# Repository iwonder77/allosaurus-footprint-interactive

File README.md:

# Allosaurus Footprint Stomp Pad Interactive

Three-channel, optically-isolated 24 V input board plus ESP32 show controller that turns industrial safety mats ("stomp pads") into clean, debounced triggers for synchronized video and LED strip output at the Need for Speed exhibit in Thanksgiving Point's Museum of Ancient Life. A visitor stomps a footprint mat, and the matching dinosaur's clip plays with an accompanying light strip animation around that Allosaurus' femur bone cast.

---

## At a Glance

|                       |                                                                                                 |
| --------------------- | ----------------------------------------------------------------------------------------------- |
| **Input domain**      | 24 V DC current loop, one per mat (field wiring, up to ~10 ft)                                  |
| **Logic domain**      | 3.3 V, shared with the controller (no level shifting needed)                                    |
| **Channels / mats**   | 3 - `hatchling`, `juvenile`, `adult` (one per footprint mat)                                    |
| **Input per channel** | ASOSafety safety mat (normally-open, passive dry contact)                                       |
| **Isolation**         | onsemi **H11L1M** optocoupler - one per channel                                                 |
| **Controller**        | **ESP32-DevKitC** (`fqbn: esp32:esp32:esp32`) firmware sketch in `esp32/`                       |
| **Input logic**       | Mat pressed → `Vo` LOW (**active-low**, external pull-up idles HIGH)                            |
| **Output banks**      | Media (BrightSign) + LED Light Strip (controlled by QuinLED), both **active-low** 200 ms pulses |
| **Show rule**         | First stomp wins; all mats locked out until that clip finishes                                  |
| **PCB**               | `2-layer, JLCPCB fab + assembly`                                                                |
| **Status**            | PCB version June 2026 designed (see `ERRATA.md`) · firmware complete                            |

---

---

## Overview

The Allosaurus Footprint interactive lets visitors stomp on floor-mounted pads to trigger a short video, audio, and light response - a video clip on a BrightSign player and an LED-strip animation on a QuinLED driver - fired in sync from a single step. Each pad is an **industrial normally-open safety mat used here purely as a rugged foot switch** in order to run unattended 24/7 in an abusive museum exhibit environment.

The obvious approach is to wire each mat's dry contact straight into a GPIO with the internal pull-up and debounce in firmware. That may work on a bench, but is not the bullet proof solution on the floor for the following reasons:

- The mats sit **up to ~10 ft** from the controller.
- The exhibit must run **24/7, unattended, for years**, with **hundreds of activations a day** and cannot experience any brown-out or mat trigger failures.
- Hundreds of visitors means hundreds of potential **ESD events** onto the mat wiring.
- Industrial-rated mats need a "wetting" current to ensure reliable long-term operation of the dry contacts (part of the reason manufacturers specify connecting to a 24V system)

A bare high-impedance GPIO sense on a 10 ft run is an antenna prone to noise pickup and false triggers. The optoisolation board I designed was a cheap bulletproof add-on to solves both problems at the input stage, so the controller only ever sees a clean, isolated, logic-level edge - then the firmware does debounce, fault detection, and show sequencing on top.

---

# Hardware

## Hardware Design Requirements

The input board needed to:

- Convert a passive N.O. mat closure into a reliable 3.3 V logic trigger.
- Provide **galvanic isolation** between the 24 V field wiring and the 3.3 V logic, so ground offsets and transients on the mat side cannot reach the MCU.
- Resist false triggers from noise coupled onto the long mat cabling.
- Give maintenance staff a **visible per-channel indicator** to confirm at a glance that a mat is being pressed and its sense path is driven.
- Be manufacturable at JLCPCB (fab + assembly) with clean, auditable part placement and silkscreen labels.
- Run for years with essentially zero maintenance.

These led to a **24 V current loop driving an optocoupler per channel**: the current loop resists noise, adds a bit of "wetting" current, and the optocoupler provides isolation plus a clean Schmitt-trigger output edge for the show controller.

## Main Hardware Components

- onsemi **H11L1M** optocoupler - integrated **Schmitt-trigger, open-collector, logic-compatible** output
- **1N4148W** small-signal diode - reverse-polarity protection across the optocoupler input
- Visible indicator LED (green SMD) - per channel, on the input side
- Current-limiting resistors, pull-up resistors, decoupling/filter capacitors (see **Design Notes**)

The full BOM lives in `manufacturing/`.

## Full Schematic

## Main Hardware Architecture

The three channels are identical.

**Input side (referenced to `GND1`, the 24 V ground):**

```
+24V ── mat (N.O.) ── R_series ── [indicator LED] ── H11L1M IR LED ── GND1
                 └── D2 (1N4148W) across the LED string, reverse protection
```

While someone stands on the mat the contact closes and current flows, driving the H11L1M input IR LED and lighting the visible indicator - so the indicator doubles as direct confirmation the sense LED is driven.

> **Note:** rev 1 places the indicator LED _in series_ with the IR LED. This works but is being revised to a parallel branch - see **Hardware Revisions** and `ERRATA.md`.

**Output side (referenced to `GND2`, the 3.3 V ground):**

```
+3V3 ── R_pullup (2.2 kΩ) ──┬── Vo (H11L1M open-collector) ── ESP32 GPIO
                            └── C1 (0.1 µF) noise filter to GND2
+3V3 ── C2 (0.1 µF) decoupling, close to the H11L1M VCC pin ── GND2
```

The output is **active-low on a press**: pressed → IR LED on → output transistor on → `Vo` LOW. Idle → `Vo` pulled HIGH by the 2.2 kΩ. The output-side `VCC` shares the 3.3 V rail with the MCU so HIGH can never exceed the MCU input rail.

| Mat state        | IR LED | `Vo` node      | GPIO reads | Indicator LED |
| ---------------- | ------ | -------------- | ---------- | ------------- |
| Idle (open)      | off    | HIGH (~3.07 V) | HIGH       | off           |
| Pressed (closed) | on     | LOW (≤ 0.4 V)  | LOW        | lit           |

## Design Notes

### Why a 24 V current loop instead of a bare GPIO

**Current loop, not voltage sense.** Pushing real current (target ~9–10 mA) through the H11L1M input LED is a low-impedance path; noise must overcome actual current to look like a valid change. Far harder to corrupt than a voltage on a high-impedance node over 10 ft.

**Wetting current (bonus).** Meaningful current through the dry mat contacts keeps a **wetting current** flowing, which helps those contacts resist any oxide film that makes aging switches flaky. This sets a _floor_ on the sense-branch current independent of the opto's switching threshold.

### Optocoupler output logic and levels

The H11L1M's integrated Schmitt trigger gives clean, bounce-free edges. Verified against the controller's input thresholds (ESP32 input thresholds are ratios of VDD):

| Parameter                           | Value   | Source                               |
| ----------------------------------- | ------- | ------------------------------------ |
| `V_IH(min)` ≈ 0.75·VDD              | ~2.48 V | ESP32 datasheet                      |
| `V_IL(max)` ≈ 0.25·VDD              | ~0.83 V | ESP32 datasheet                      |
| H11L1M `V_OL`                       | ≤ 0.4 V | datasheet (sinks 16 mA at 0.4 V max) |
| H11L1M output-off leakage `I_OH`    | 100 µA  | datasheet                            |
| H11L1M `V_CC` range (min **3.0 V**) | 3–16 V  | datasheet                            |

With a **2.2 kΩ pull-up**: HIGH ≈ 3.3 − (~105 µA)(2.2 kΩ) ≈ **3.07 V** (~0.6 V over `V_IH`); LOW ≤ **0.4 V** (~0.4 V under `V_IL`); pressed-state sink ≈ 1.3 mA (far below 16 mA). The binding constraint is the HIGH side — the 100 µA leakage droops it — so the pull-up is kept small-ish. `C1` = 0.1 µF with the 2.2 kΩ gives RC ≈ **220 µs**: a **glitch filter, not a debouncer**. Mat bounce runs for milliseconds, so firmware debounce is still mandatory (and the firmware does far more than that - see below).

### Reverse-polarity protection

The 1N4148W spans the forward LED string, reverse-biased in normal use, conducting only on a reversed-polarity miswire. Confirm its orientation (cathode toward +24 V in normal operation). A single series Schottky on the 24 V input is the tidier belt-and-suspenders option if full reverse immunity is ever wanted.

## Hardware Revisions

Two changes are planned for the next board spin. **version June 2026 is functional as-is** - these are improvements, not blockers. Full detail, rationale, and selection guidance live in **[`ERRATA.md`](./ERRATA.md)** next to the rev-1 schematic/PCB files.

- **ERRATA-1: Indicator LED should be parallel, not series.** Version June 2026 shares one loop current between the IR LED and the indicator. Moving the indicator to its own parallel branch (each LED with its own resistor) lets each current be sized independently and stops an open-failed indicator from killing the sense path. **Recompute the opto current when you do**.
- **ERRATA-2: Add a TVS at each mat connector.** Given public foot traffic (ESD) over ~10 ft of exposed cable, 24/7 for years, a unidirectional TVS at each input protects the front-end. (It does _not_ protect the ESP32 - the opto already does that.) Recommended, not required.

## PCB & Manufacturing

**Isolation strategy (the whole point).** `GND1` (24 V) and `GND2` (3.3 V) are separate nets that **never** connect on the board - the only crossing is the opto's light barrier. Two separate bottom-layer copper pours with a ~3 mm gap, the barrier line running through each optocoupler, all three optos oriented identically.

**Mounting holes - verified safe.** The four corner holes carry **no copper** and take plastic standoffs for a custom 3D-printed mount, so hardware can't bridge `GND1` to `GND2`.

**Net classes**

| Class        | Track width | Nets                 |
| ------------ | ----------- | -------------------- |
| `Input_24V`  | 0.5 mm      | `+24V`, `GND1`       |
| `Output_3V3` | 0.3 mm      | `+3V3`, `GND2`, `Vo` |

Both share via 0.6 mm / hole 0.3 mm (0.15 mm annular) and 0.3 mm clearance.

---

# Firmware

`esp32/` — a single non-blocking sketch that reads the three mats, validates each stomp, and fires the matching media + light triggers. No RTOS tasks, no delays; `loop()` runs the whole thing and feeds a hardware watchdog every pass.

## Pinout — `esp32/`

All constants live in `src/Config.h`. Index `i` ties together input `[i]`, media `[i]`, and light `[i]` (mat 1 = hatchling, 2 = juvenile, 3 = adult).

| GPIO     | Direction           | Connects to                         | Constant                |
| -------- | ------------------- | ----------------------------------- | ----------------------- |
| 13       | Input (active-low)  | `Vo1` - hatchling opto output       | `MAT_INPUT_PINS[0]`     |
| 14       | Input (active-low)  | `Vo2` - juvenile opto output        | `MAT_INPUT_PINS[1]`     |
| 15       | Input (active-low)  | `Vo3` - adult opto output           | `MAT_INPUT_PINS[2]`     |
| 21       | Output (active-low) | BrightSign trigger - hatchling clip | `MEDIA_TRIGGER_PINS[0]` |
| 22       | Output (active-low) | BrightSign trigger - juvenile clip  | `MEDIA_TRIGGER_PINS[1]` |
| 23       | Output (active-low) | BrightSign trigger - adult clip     | `MEDIA_TRIGGER_PINS[2]` |
| 16       | Output (active-low) | QuinLED trigger - hatchling strip   | `LIGHT_TRIGGER_PINS[0]` |
| 17       | Output (active-low) | QuinLED trigger - juvenile strip    | `LIGHT_TRIGGER_PINS[1]` |
| 18       | Output (active-low) | QuinLED trigger - adult strip       | `LIGHT_TRIGGER_PINS[2]` |
| 25/26/27 | _reserved_          | former audio bank (WAV Trigger)     | - (do not reuse)        |

## Behavior

**Debounce / validation (per mat).** Three independent timing knobs in `Config.h`, each rejecting a different failure mode — deliberately not collapsed into one value:

| Knob              | Default | Rejects                                                                                 |
| ----------------- | ------- | --------------------------------------------------------------------------------------- |
| `MAT_DEBOUNCE_MS` | 10 ms   | fast edge chatter - line must be stable this long                                       |
| `MAT_MIN_ON_MS`   | 30 ms   | short spikes - press must dwell this long to count (≥ debounce); also the event latency |
| `MAT_REARM_MS`    | 80 ms   | bouncy releases - line must read clear this long to re-arm                              |

**One video at a time (global lockout).** The first validated stomp wins: its clip is triggered and **every** mat input is ignored until that clip finishes, so a video always plays start-to-finish and is never cut off or re-triggered. Lockout = `VIDEO_LENGTH_MS[i]` (13 / 17 / 22 s) + `RETRIGGER_HEADROOM_MS` (1 s) → ~14 / 18 / 23 s. A stomp arriving during a lockout is **discarded**, not queued. This is a different mechanism from `MAT_REARM_MS` (a low-level per-mat cooldown).

**Fail-closed detection.** If a mat reads active continuously for `MAT_STUCK_MS` (10 s - far longer than any real stomp: a welded contact, a stuck mat, or a shorted line), that mat is flagged **faulted**: it stops emitting events and its outputs are forced idle so a stuck input can't leave a device asserted. It auto-recovers after the line reads clear for `MAT_FAULT_RECOVER_MS` (500 ms), re-arming through the boot-safe path.

**Boot-safe.** Each detector starts in `WaitForRelease`, so a mat already held down at power-on never produces a spurious event - it arms only after a confirmed clean release.

**Watchdog.** `loop()` is fully non-blocking and feeds the task watchdog (TWDT) every pass. If anything ever wedges the main task past `WDT_TIMEOUT_MS` (5 s), the watchdog panics and resets the board - the exhibit self-recovers instead of hanging.

## Architecture

The `.ino` handles bring-up (pin setup, watchdog subscribe) and the per-mat loop; the real press logic lives in `src/`.

- **`MatInput`**: a non-blocking, debounced press detector for one active-low opto input, owning only its own state machine (no dependency on Serial or the outputs). `update()` advances it, `eventFired()` latches true exactly once per validated stomp (reading clears it), `pressed()` / `faulted()` / `rawActive()` expose state. The FSM: `WaitForRelease → Armed → PressDebounce → PressConfirm → Held`, with `Faulted` entered from anywhere on a stuck line. Fault and min-on timing are measured against `millis()` marks, so nothing blocks.
- **Main sketch (`esp32.ino`)**: owns one `MatInput` per mat and two output banks (`BANK_MEDIA`, `BANK_LIGHT`) in an index-aligned table, so `triggerMat(i)` fires both of mat `i`'s lines at once and `serviceOutputs()` returns each to idle after the pulse width — non-blocking, so mat scanning never stalls behind an in-flight pulse. It owns the global lockout, logs faults/recoveries once on their edge, and forces a faulted mat's outputs idle. The lockout comparison is rollover-safe (`(int32_t)(now - lockoutUntil) >= 0`).
- **`Config.h`**: single source of truth for pins, polarity, and all timing. `constexpr` throughout (compile-time, zero RAM). Everything you'd tune on the bench lives here so the logic modules stay untouched.

## Deployment & Bring-up

### Flashing

Platform is set in `sketch.yaml` (`esp32:esp32:esp32`). `default_port` is committed as `/dev/cu.usbserial-0001` - **change it to your machine's serial port**, or pass `-p <port>` on upload. A plain `arduino-cli compile` / `upload` builds and flashes the sketch.

### Tuning on the real mat

Leave `SERIAL_LOG_EVENTS = true` and watch the serial console at **115200**. Then:

- **Double-triggers on one stomp** → increase `MAT_DEBOUNCE_MS` (and/or `MAT_REARM_MS`).
- **Missed / dropped stomps** → decrease `MAT_MIN_ON_MS` (keep it ≥ `MAT_DEBOUNCE_MS`).
- Set `VIDEO_LENGTH_MS[]` to the **real** clip durations per mat - these drive the lockout, so a value shorter than the clip will let the exhibit re-arm mid-video.

### What working looks like

| Event             | Serial line                                                                           |
| ----------------- | ------------------------------------------------------------------------------------- |
| Boot              | `Allosaurus Footprint Interactive - ready`                                            |
| Valid stomp       | `Mat N triggered (input GPIO .. -> media .. / light ..); ignoring all mats for .. ms` |
| Stuck mat / short | `FAULT: Mat N stuck active (input GPIO ..) - check for a failed-closed mat/short`     |
| Fault clears      | `RECOVERED: Mat N back to normal (input GPIO ..)`                                     |

### When something is wrong

| Symptom                                            | Likely cause                              | Check                                                                                |
| -------------------------------------------------- | ----------------------------------------- | ------------------------------------------------------------------------------------ |
| A mat never triggers                               | Input wiring / opto / that mat            | Does the on-board indicator LED light on press? Is `Vo` reaching the right GPIO?     |
| A stomp fires media but not lights (or vice-versa) | One output bank's wire                    | That mat's `MEDIA`/`LIGHT` GPIO to the device input, plus common ground              |
| Downstream device never reacts to a pulse          | Polarity / reference mismatch             | Device must trigger on an **active-LOW** pulse and share ground; input must be 3.3 V |
| `FAULT: Mat N stuck active` on repeat              | Welded contact, stuck mat, or shorted run | Inspect that mat and its cable; fault clears itself once the line reads clear        |
| Exhibit ignores stomps for ~15–25 s                | **Not a fault** — global lockout          | A clip is playing; by design all mats are ignored until it ends                      |
| Board reboots every few seconds                    | Watchdog fired — `loop()` stalled         | Something is blocking the main task; check recent changes / peripherals              |

### Quirks worth knowing

- **Simultaneous stomps: first wins.** If two mats are hit close together, only the first registers; the rest are ignored (not queued) until the clip finishes. Intended - one video at a time.
- **A stomp during a video does nothing.** Discarded, not buffered, so the exhibit never "fires late" when the lockout ends.
- **Audio is not wired.** An audio bank (SparkFun + Robertsonics WAV Trigger) was prototyped and removed; GPIO 25/26/27 are reserved. To restore it, re-add `AUDIO_TRIGGER_PINS[] = {25, 26, 27}`, its `static_assert`, and a `BANK_AUDIO` entry in `OUTPUT_BANK_PINS`.

---

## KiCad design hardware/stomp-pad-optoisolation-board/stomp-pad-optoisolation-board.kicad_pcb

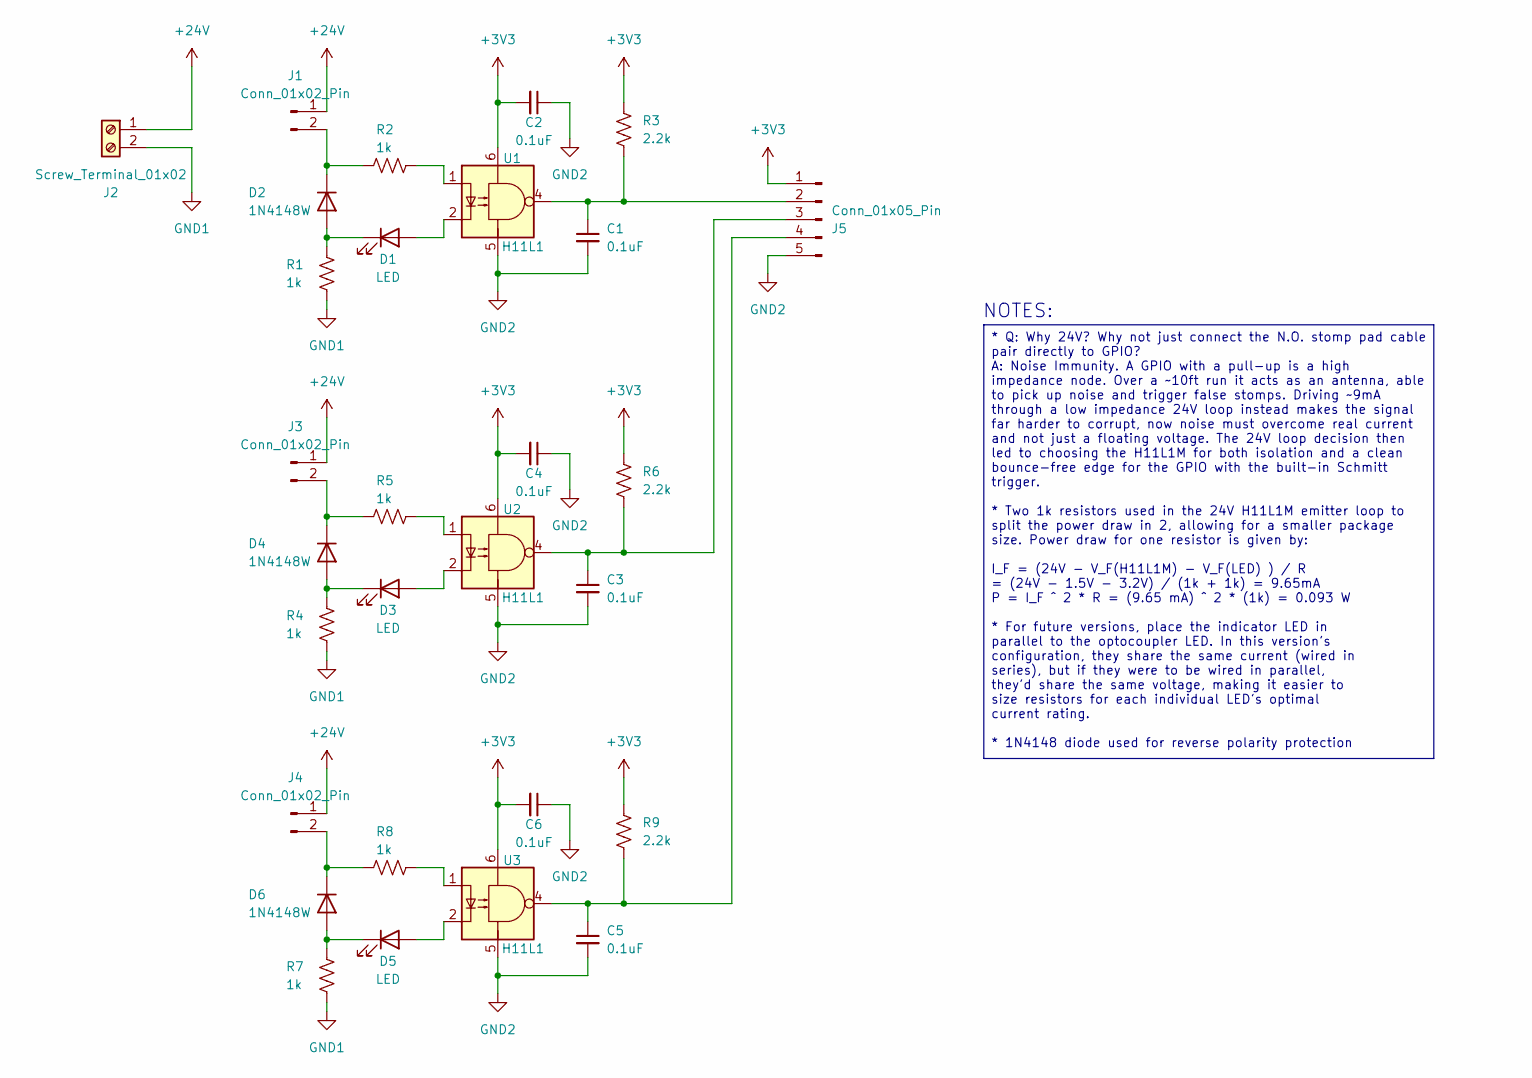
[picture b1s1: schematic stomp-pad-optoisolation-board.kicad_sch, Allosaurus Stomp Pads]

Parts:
C1, C2, C3, C4, C5, C6: 0.1uF; C_0603_1608Metric
D1, D3, D5: LED; LED_1206_3216Metric
D2, D4, D6: 1N4148W; D_SOD-123
J1, J3, J4: Conn_01x02_Pin; PinHeader_1x02_P2.54mm_Vertical
J2: Screw_Terminal_01x02; PhoenixContact_MC_1,5_2-G-3.5_1x02_P3.50mm_Horizontal
J5: Conn_01x05_Pin; PinHeader_1x05_P2.54mm_Vertical
R1, R2, R4, R5, R7, R8: 1k; R_1206_3216Metric
R3, R6, R9: 2.2k; R_0805_2012Metric
U1, U2, U3: H11L1; DIP-6_W7.62mm_LongPads

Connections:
+3V3: C2.2, C4.2, C6.2, J5.1, R3.1, R6.1, R9.1, U1.6, U2.6, U3.6
+24V: J1.1, J2.1, J3.1, J4.1
GND1: J2.2, R1.1, R4.1, R7.1
GND2: C1.2, C2.1, C3.2, C4.1, C5.2, C6.1, J5.5, U1.5, U2.5, U3.5
unnamed: D1.2 (A), U1.2
unnamed: D1.1 (K), D2.2 (A), R1.2
unnamed: D2.1 (K), J1.2, R2.1
unnamed: D3.2 (A), U2.2
unnamed: D3.1 (K), D4.2 (A), R4.2
unnamed: D4.1 (K), J3.2, R5.1
unnamed: D5.2 (A), U3.2
unnamed: D5.1 (K), D6.2 (A), R7.2
unnamed: D6.1 (K), J4.2, R8.1
unnamed: C1.1, J5.2, R3.2, U1.4
unnamed: C3.1, J5.3, R6.2, U2.4
unnamed: C5.1, J5.4, R9.2, U3.4
unnamed: R2.2, U1.1
unnamed: R5.2, U2.1
unnamed: R8.2, U3.1

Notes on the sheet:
NOTES:
* Q: Why 24V? Why not just connect the N.O. stomp pad cable pair directly to GPIO? A: Noise Immunity. A GPIO with a pull-up is a high impedance node. Over a ~10ft run it acts as an antenna, able to pick up noise and trigger false stomps. Driving ~9mA through a low impedance 24V loop instead makes t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

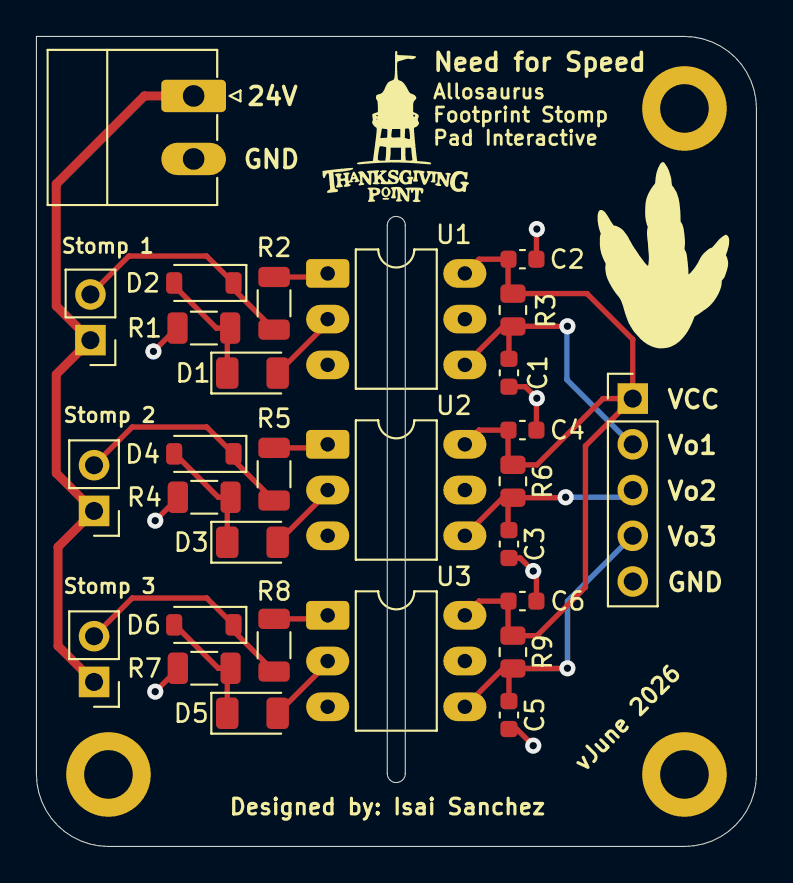
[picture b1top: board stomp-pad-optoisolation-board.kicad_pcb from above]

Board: 2 copper layers, 40.0 x 45.0 mm, 29 parts (0 on the bottom side), 19 nets.
